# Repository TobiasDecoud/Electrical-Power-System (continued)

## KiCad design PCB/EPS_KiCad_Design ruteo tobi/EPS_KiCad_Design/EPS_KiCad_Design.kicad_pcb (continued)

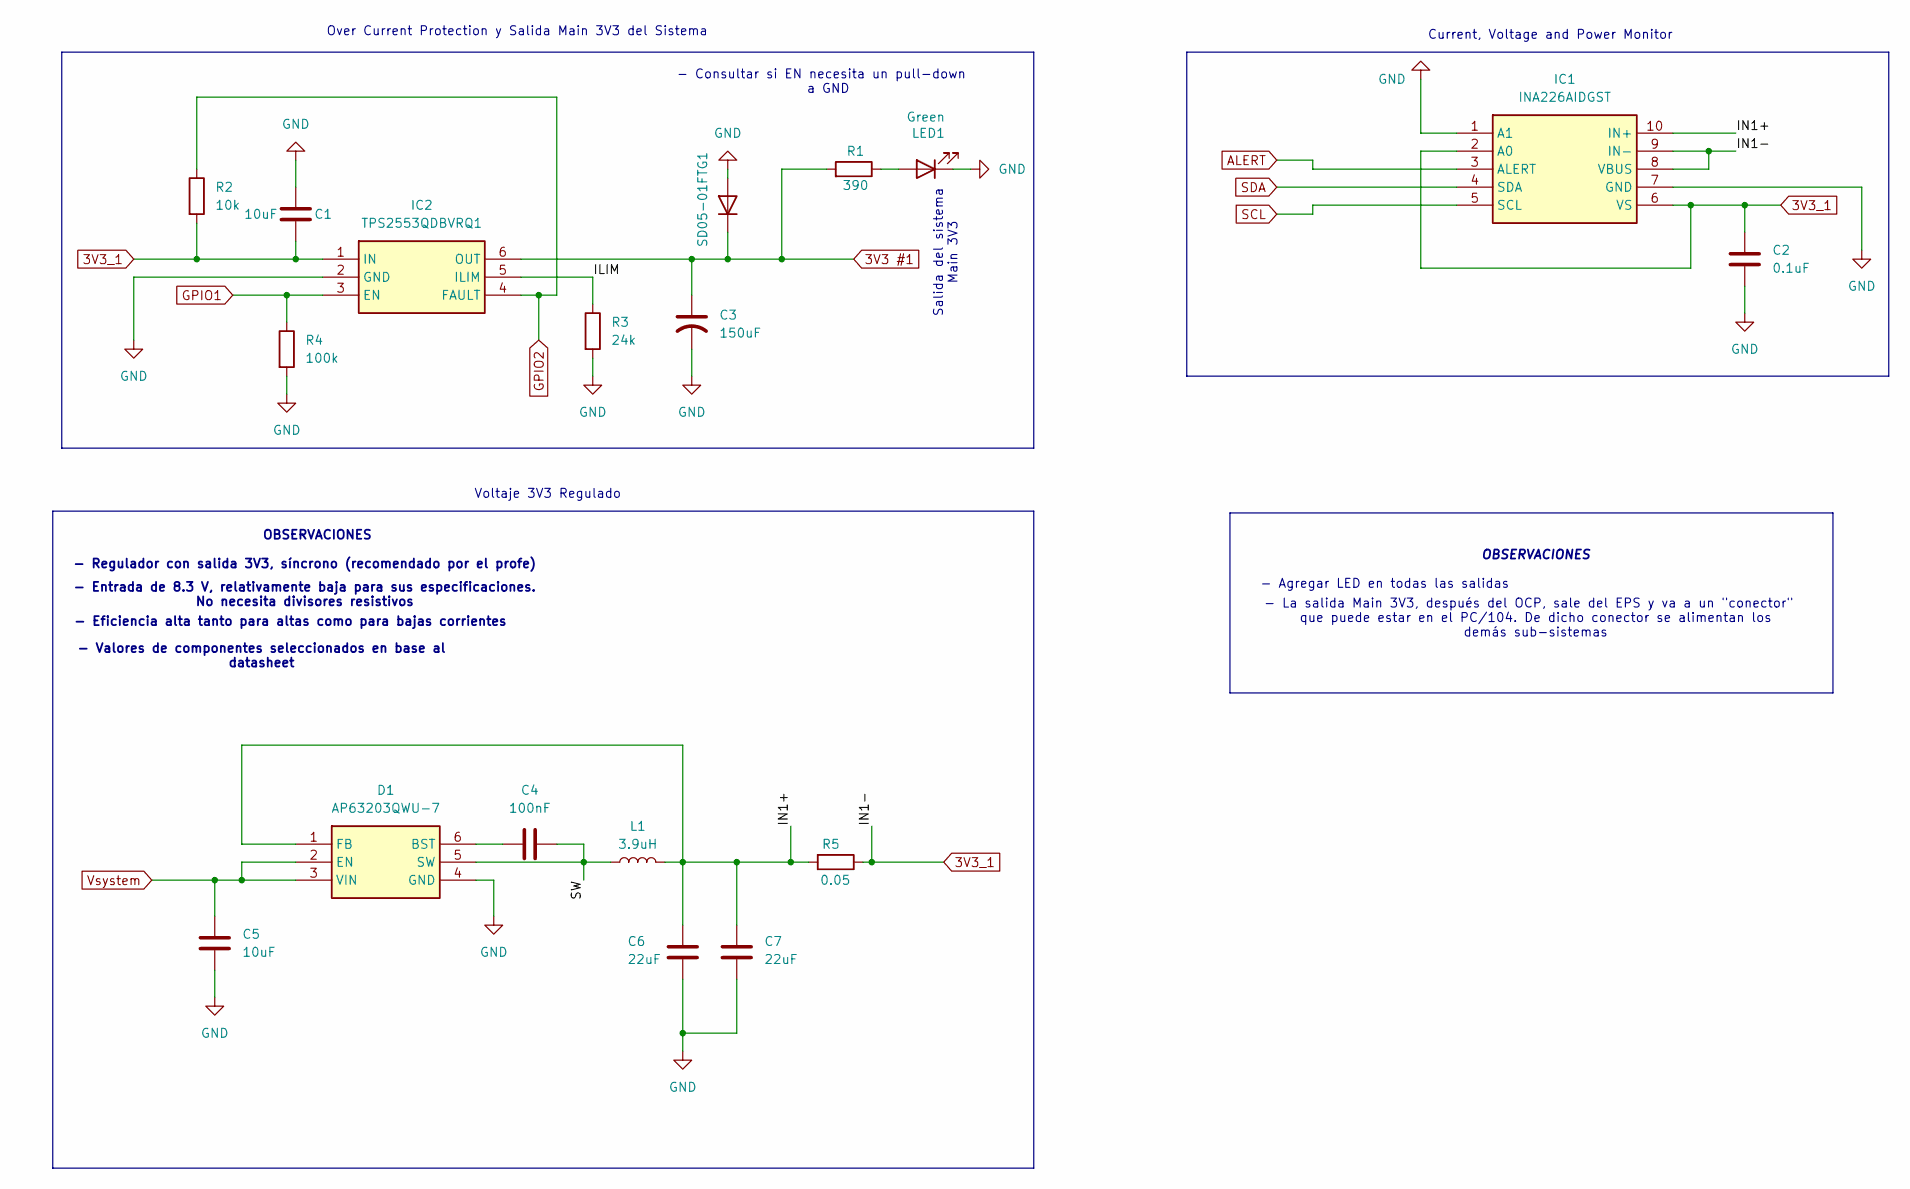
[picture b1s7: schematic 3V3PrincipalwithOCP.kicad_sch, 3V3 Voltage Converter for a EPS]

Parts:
C1, C5: 10uF; C_0805_2012Metric_Pad1.18x1.45mm_HandSolder
C2: 0.1uF; C_0805_2012Metric_Pad1.18x1.45mm_HandSolder
C3: 150uF; CAPPM3528X210N
C4: 100nF; C_0805_2012Metric_Pad1.18x1.45mm_HandSolder
C6, C7: 22uF; C_0805_2012Metric_Pad1.18x1.45mm_HandSolder
D1: AP63203QWU-7; SOT95P280X100-6N; Mouser Part Number 621-AP63203QWU-7
IC1: INA226AIDGST; SOP50P490X110-10N; Mouser Part Number 595-INA226AIDGST
IC2: TPS2553QDBVRQ1; SOT95P280X145-6N; Mouser Part Number 595-TPS2553QDBVRQ1
L1: 3.9uH; ASPI0628150MT1
LED1: Green; LED_0805_2012Metric_Pad1.15x1.40mm_HandSolder
R1: 390; R_0805_2012Metric_Pad1.20x1.40mm_HandSolder
R2: 10k; R_0805_2012Metric_Pad1.20x1.40mm_HandSolder
R3: 24k; R_0805_2012Metric_Pad1.20x1.40mm_HandSolder
R4: 100k; R_0805_2012Metric_Pad1.20x1.40mm_HandSolder
R5: 0.05; R_0805_2012Metric_Pad1.20x1.40mm_HandSolder
SD05-01FTG1: D; SOD2613X114N

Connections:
3V3 #1: C3.1, IC2.6 (OUT), R1.2, SD05-01FTG1.1 (K); also elsewhere on the board
3V3_1: C1.1, C2.1, IC1.2 (A0), IC1.6 (VS), IC1.8 (VBUS), IC1.9 (IN-), IC2.1 (IN), R2.2, R5.1; also elsewhere on the board
/Voltage Converter/3V3 Principal + OCP/ILIM: IC2.5 (ILIM), R3.1
/Voltage Converter/3V3 Principal + OCP/IN1+: C6.1, C7.1, D1.1 (FB), IC1.10 (IN+), L1.2, R5.2
/Voltage Converter/3V3 Principal + OCP/SW: C4.2, D1.5 (SW), L1.1
ALERT: IC1.3 (ALERT); also elsewhere on the board
GND: C1.2, C2.2, C3.2, C5.2, C6.2, C7.2, D1.4 (GND), IC1.1 (A1), IC1.7 (GND), IC2.2 (GND), LED1.1 (K), R3.2, R4.2, SD05-01FTG1.2 (A); also elsewhere on the board
GPIO1: IC2.3 (EN), R4.1; also elsewhere on the board
GPIO2: IC2.4 (FAULT), R2.1; also elsewhere on the board
unnamed: C4.1, D1.6 (BST)
unnamed: LED1.2 (A), R1.1
SCL: IC1.5 (SCL); also elsewhere on the board
SDA: IC1.4 (SDA); also elsewhere on the board
Vsystem: C5.1, D1.2 (EN), D1.3 (VIN); also elsewhere on the board

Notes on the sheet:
- Consultar si EN necesita un pull-down a GND
Voltaje 3V3 Regulado
Current, Voltage and Power Monitor
- Entrada de 8.3 V, relativamente baja para sus especificaciones. No necesita divisores resistivos
- Regulador con salida 3V3, síncrono (recomendado por el profe)
- Eficiencia alta tanto para altas como para bajas corrientes
OBSERVACIONES
- Valores de componentes seleccionados en base al datasheet
Salida del sistema Main 3V3
Over Current Protection y Salida Main 3V3 del Sistema
- Agregar LED en todas las salidas
- La salida Main 3V3, después del OCP, sale del EPS y va a un "conector" que puede estar en el PC/104. De dicho conector se alimentan los demás sub-sistemas

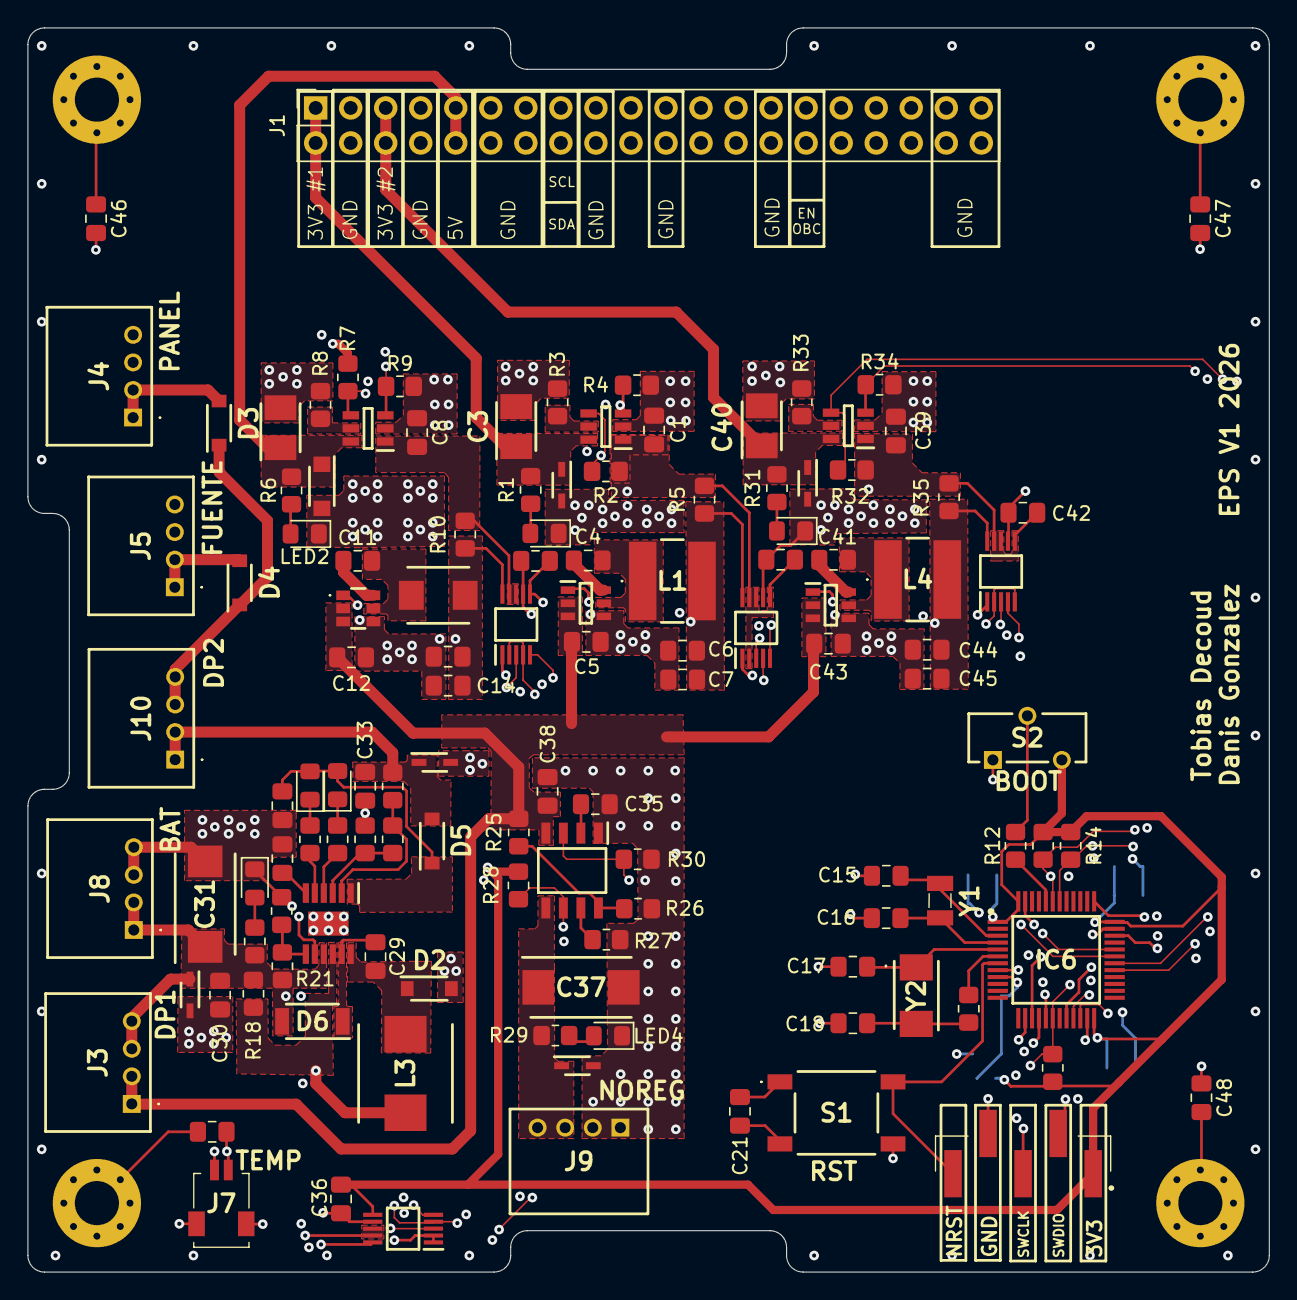
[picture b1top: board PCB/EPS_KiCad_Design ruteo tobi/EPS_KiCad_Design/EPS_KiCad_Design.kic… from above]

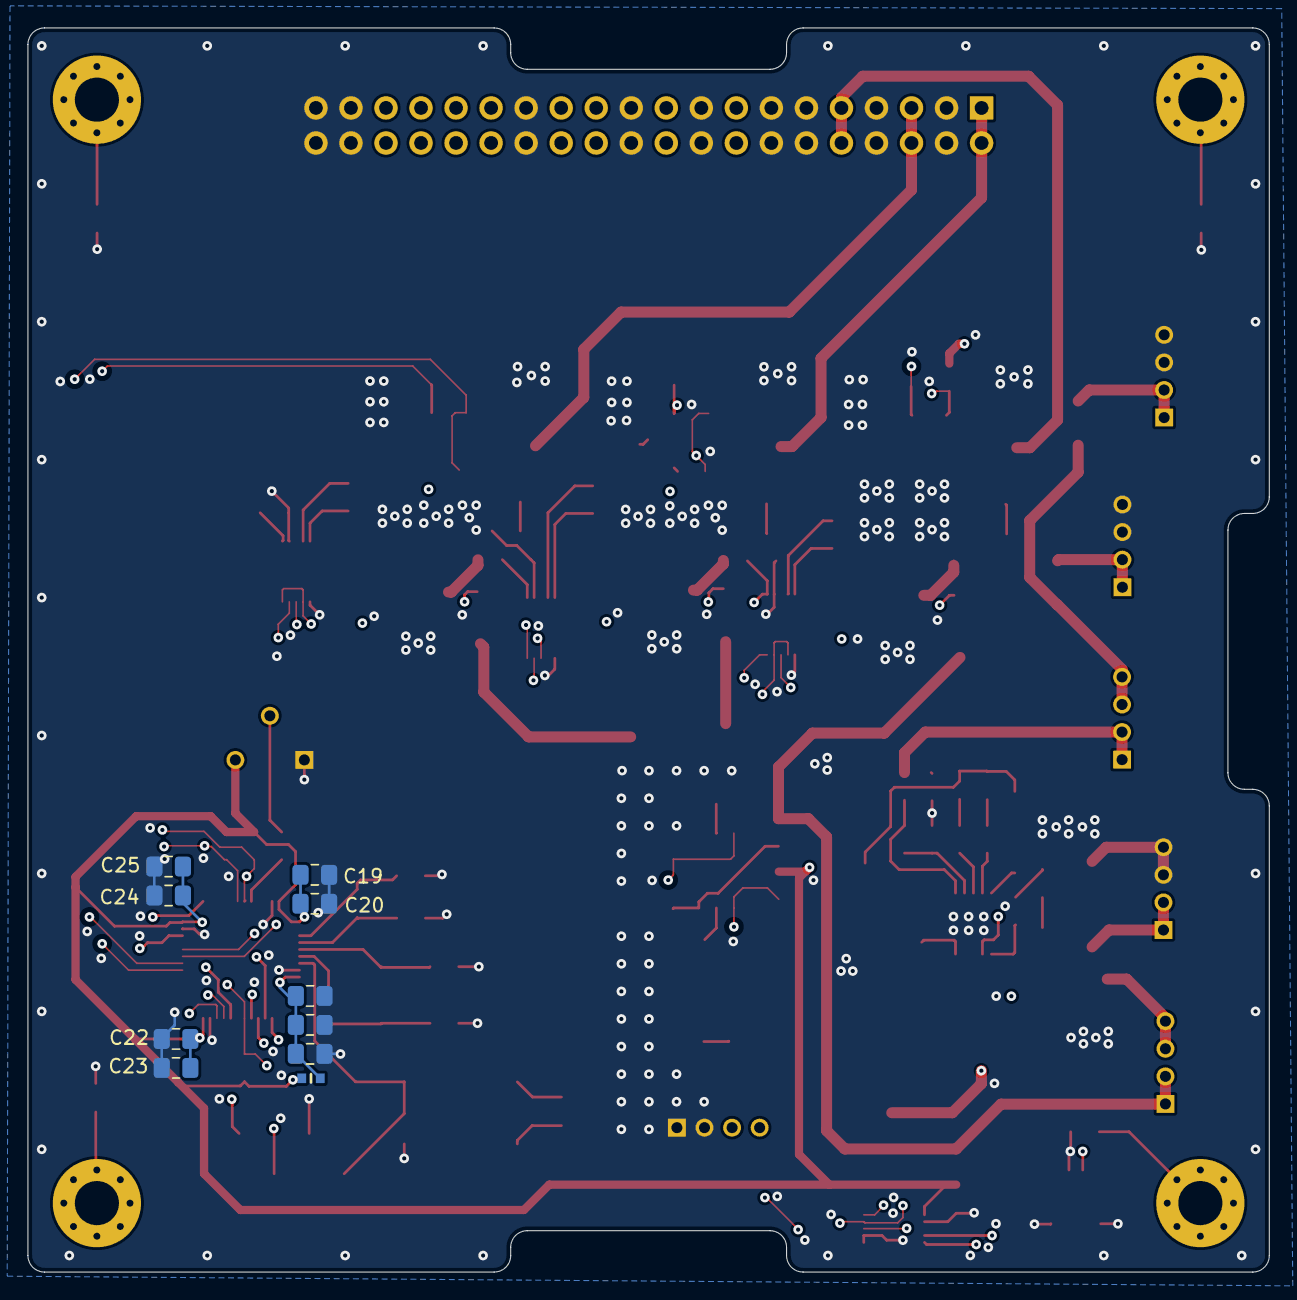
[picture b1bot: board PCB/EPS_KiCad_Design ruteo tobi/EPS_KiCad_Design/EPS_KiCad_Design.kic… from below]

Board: 4 copper layers, 90.0 x 90.2 mm, 137 parts (10 on the bottom side), 78 nets.

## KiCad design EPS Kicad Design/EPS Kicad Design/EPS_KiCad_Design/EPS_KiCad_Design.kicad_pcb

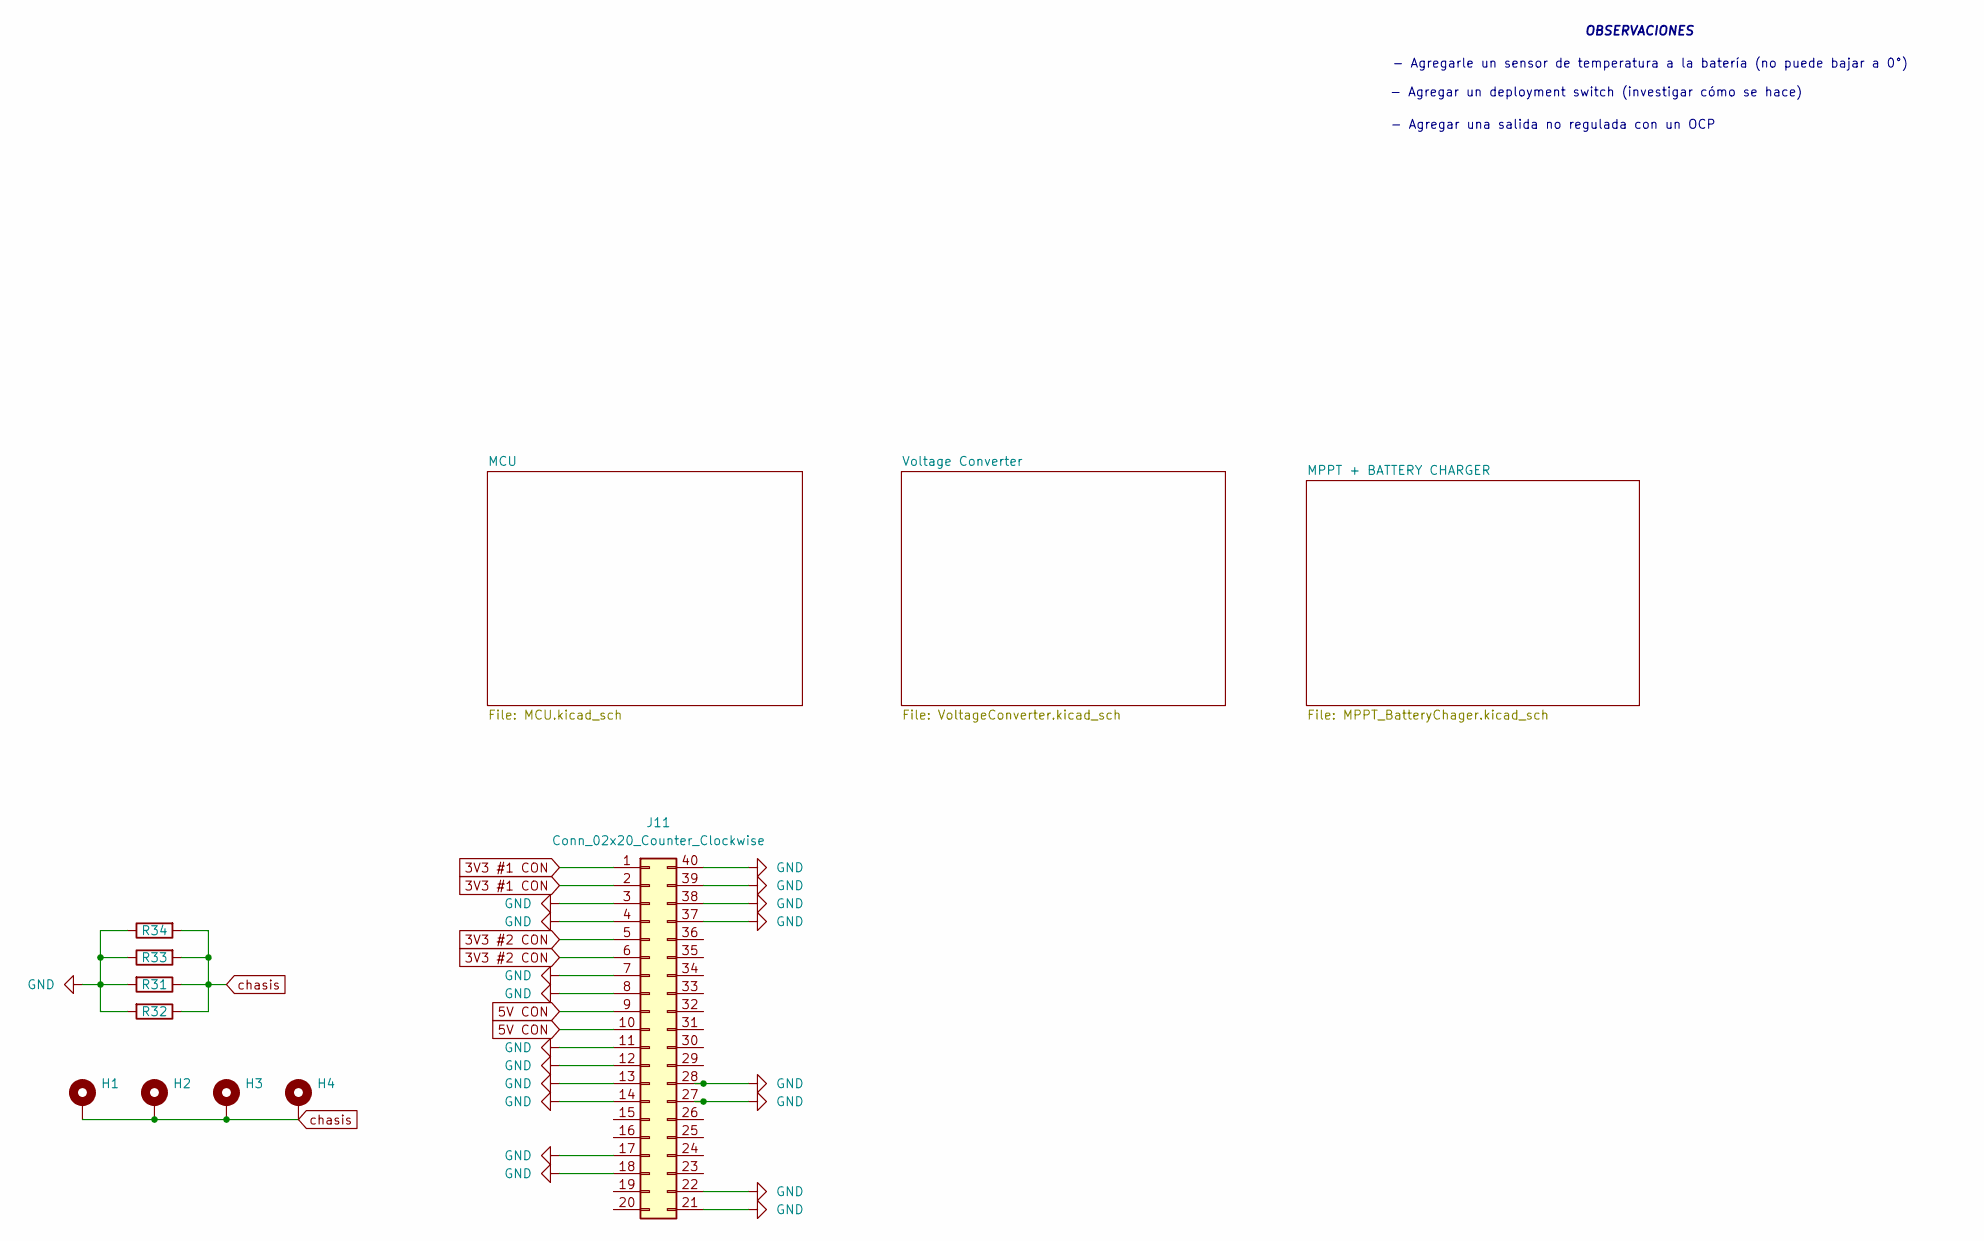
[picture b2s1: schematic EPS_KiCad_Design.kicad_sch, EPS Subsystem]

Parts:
H1, H2, H3, H4: MountingHole_Pad
J11: Conn_02x20_Counter_Clockwise; PinSocket_2x20_P2.54mm_Vertical
R31, R32, R33, R34: R_0805_2012Metric_Pad1.20x1.40mm_HandSolder

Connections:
3V3 #1 CON: J11.1, J11.2; also elsewhere on the board
3V3 #2 CON: J11.5, J11.6; also elsewhere on the board
5V CON: J11.9, J11.10; also elsewhere on the board
GND: J11.3, J11.4, J11.7, J11.8, J11.11, J11.12, J11.13, J11.14, J11.17, J11.18, J11.21, J11.22, J11.27, J11.28, J11.37, J11.38, J11.39, J11.40, R31.2, R32.2, R33.1, R34.1; also elsewhere on the board
chasis: H1.1, H2.1, H3.1, H4.1, R31.1, R32.1, R33.2, R34.2

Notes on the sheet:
OBSERVACIONES
- Agregar un deployment switch (investigar cómo se hace)
- Agregarle un sensor de temperatura a la batería (no puede bajar a 0°)
- Agregar una salida no regulada con un OCP

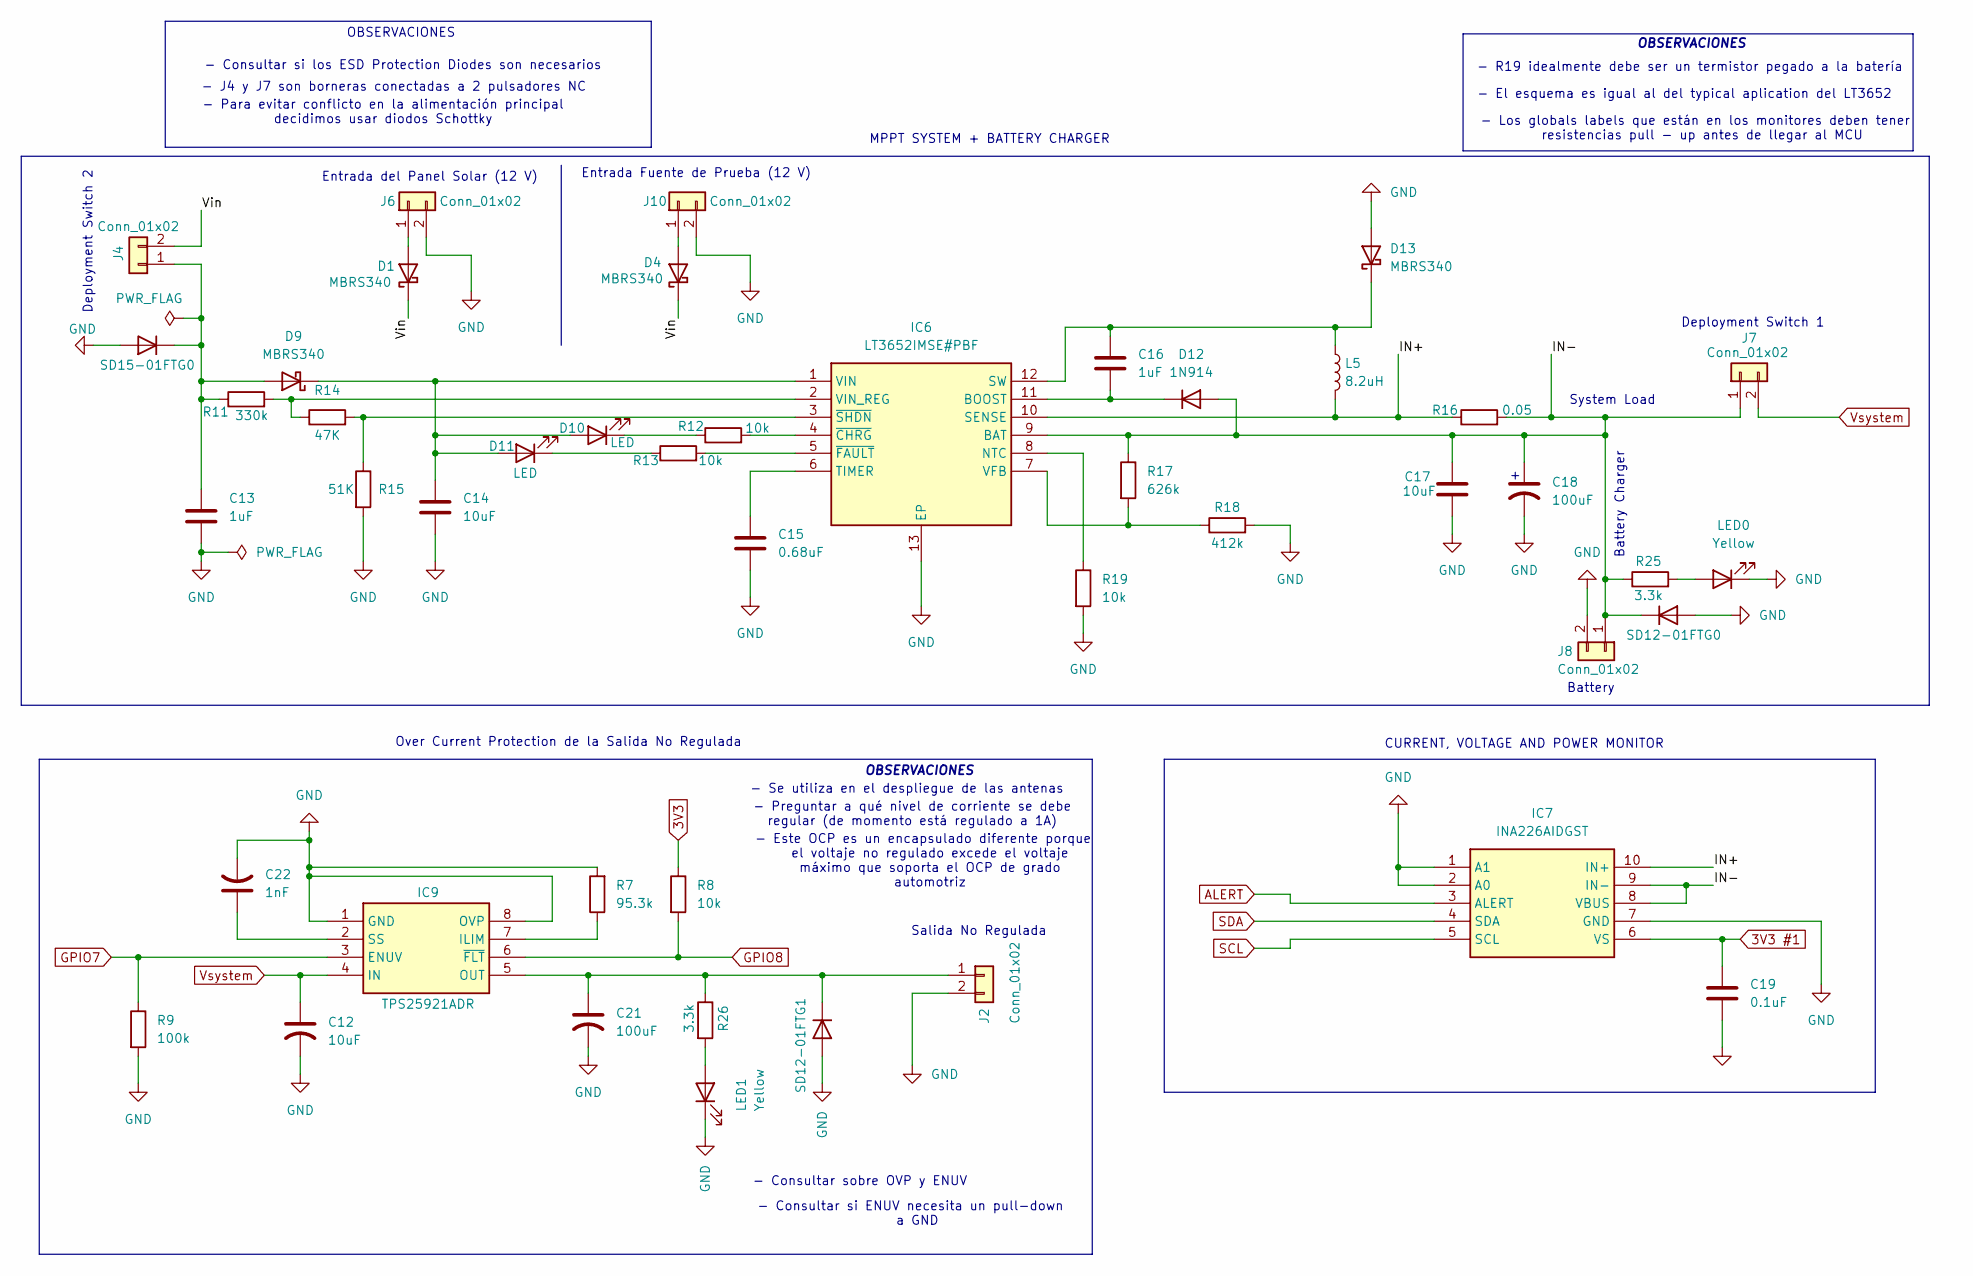
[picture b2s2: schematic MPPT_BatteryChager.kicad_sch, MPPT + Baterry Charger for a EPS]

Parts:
C12: 10uF; CP_EIA-7343-30_AVX-N_HandSolder
C13, C16: 1uF; C_0805_2012Metric_Pad1.18x1.45mm_HandSolder
C14, C17: 10uF; C_0805_2012Metric_Pad1.18x1.45mm_HandSolder
C15: 0.68uF; C_0805_2012Metric_Pad1.18x1.45mm_HandSolder
C18, C21: 100uF; CP_EIA-7343-30_AVX-N_HandSolder
C19: 0.1uF; C_0805_2012Metric_Pad1.18x1.45mm_HandSolder
C22: 1nF; CP_EIA-7343-30_AVX-N_HandSolder
D1, D4, D9, D13: MBRS340; D_SMC
D10, D11: LED; LED_0805_2012Metric_Pad1.15x1.40mm_HandSolder
D12: 1N914; 1N4148WQ13F
IC6: LT3652IMSE#PBF; SOP65P490X110-13N; Mouser Part Number 584-LT3652IMSE#PBF
IC7: INA226AIDGST; SOP50P490X110-10N; Mouser Part Number 595-INA226AIDGST
IC9: TPS25921ADR; SOIC127P600X175-8N; Mouser Part Number 595-TPS25921ADR
J2, J4, J6, J7, J8, J10: Conn_01x02
L5: 8.2uH; INDPM6965X300N
LED0, LED1: Yellow; LED_0805_2012Metric_Pad1.15x1.40mm_HandSolder
R7: 95.3k; R_0805_2012Metric_Pad1.20x1.40mm_HandSolder
R8, R12, R13, R19: 10k; R_0805_2012Metric_Pad1.20x1.40mm_HandSolder
R9: 100k; R_0805_2012Metric_Pad1.20x1.40mm_HandSolder
R11: 330k; R_0805_2012Metric_Pad1.20x1.40mm_HandSolder
R14: 47K; R_0805_2012Metric_Pad1.20x1.40mm_HandSolder
R15: 51K; R_0805_2012Metric_Pad1.20x1.40mm_HandSolder
R16: 0.05; R_2512_6332Metric_Pad1.40x3.35mm_HandSolder
R17: 626k; R_0805_2012Metric_Pad1.20x1.40mm_HandSolder
R18: 412k; R_0805_2012Metric_Pad1.20x1.40mm_HandSolder
R25, R26: 3.3k; R_0805_2012Metric_Pad1.20x1.40mm_HandSolder
SD12-01FTG0, SD12-01FTG1: SOD2613X114N
SD15-01FTG0: D; SOD2613X114N

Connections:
3V3: R8.1; also elsewhere on the board
3V3 #1: C19.1, IC7.6 (VS); also elsewhere on the board
/MPPT + BATTERY CHARGER/IN+: IC6.10 (SENSE), IC7.10 (IN+), L5.2, R16.1
/MPPT + BATTERY CHARGER/IN-: C17.1, C18.1, D12.2 (A), IC6.9 (BAT), IC7.8 (VBUS), IC7.9 (IN-), J7.1, J8.1, R16.2, R17.1, R25.1, SD12-01FTG0.1 (K)
/MPPT + BATTERY CHARGER/Vin: D1.1 (K), D4.1 (K), J4.2
ALERT: IC7.3 (ALERT); also elsewhere on the board
GND: C12.2, C13.2, C14.2, C15.2, C17.2, C18.2, C19.2, C21.2, C22.2, D13.2 (A), IC6.13 (EP), IC7.1 (A1), IC7.2 (A0), IC7.7 (GND), IC9.1 (GND), IC9.8 (OVP), J2.2, J6.2, J8.2, J10.2, LED0.1 (K), LED1.1 (K), R7.2, R9.2, R15.2, R18.2, R19.2, SD12-01FTG0.2 (A), SD12-01FTG1.2 (A), SD15-01FTG0.2 (A); also elsewhere on the board
GPIO7: IC9.3 (ENUV), R9.1; also elsewhere on the board
GPIO8: IC9.6 (~FLT), R8.2; also elsewhere on the board
unnamed: D1.2 (A), J6.1
unnamed: D4.2 (A), J10.1
unnamed: C13.1, D9.2 (A), J4.1, R11.1, SD15-01FTG0.1 (K)
unnamed: C14.1, D9.1 (K), D10.2 (A), D11.2 (A), IC6.1 (VIN)
unnamed: D10.1 (K), R12.1
unnamed: D11.1 (K), R13.1
unnamed: C16.2, D12.1 (K), IC6.11 (BOOST)
unnamed: C16.1, D13.1 (K), IC6.12 (SW), L5.1
unnamed: IC6.8 (NTC), R19.1
unnamed: C15.1, IC6.6 (TIMER)
unnamed: IC6.7 (VFB), R17.2, R18.1
unnamed: IC6.2 (VIN_REG), R11.2, R14.1
unnamed: IC6.4 (~CHRG), R12.2
unnamed: IC6.5 (~FAULT), R13.2
unnamed: IC6.3 (~SHDN), R14.2, R15.1
unnamed: IC9.7 (ILIM), R7.1
unnamed: C21.1, IC9.5 (OUT), J2.1, R26.1, SD12-01FTG1.1 (K)
unnamed: C22.1, IC9.2 (SS)
unnamed: LED0.2 (A), R25.2
unnamed: LED1.2 (A), R26.2
SCL: IC7.5 (SCL); also elsewhere on the board
SDA: IC7.4 (SDA); also elsewhere on the board
Vsystem: C12.1, IC9.4 (IN), J7.2; also elsewhere on the board

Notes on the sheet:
CURRENT, VOLTAGE AND POWER MONITOR
- Se utiliza en el despliegue de las antenas
System Load
OBSERVACIONES
Entrada del Panel Solar (12 V)
- Los globals labels que están en los monitores deben tener resistencias pull - up antes de llegar al MCU
- Para evitar conflicto en la alimentación principal decidimos usar diodos Schottky
Battery Charger
- Este OCP es un encapsulado diferente porque el voltaje no regulado excede el voltaje máximo que soporta el OCP de grado automotriz
- El esquema es igual al del typical aplication del LT3652
Over Current Protection de la Salida No Regulada
- Consultar si ENUV necesita un pull-down a GND
Deployment Switch 1
Entrada Fuente de Prueba (12 V)
Deployment Switch 2
- R19 idealmente debe ser un termistor pegado a la batería
- J4 y J7 son borneras conectadas a 2 pulsadores NC
- Consultar si los ESD Protection Diodes son necesarios
- Consultar sobre OVP y ENUV
Salida No Regulada
- Preguntar a qué nivel de corriente se debe regular (de momento está regulado a 1A)
Battery
MPPT SYSTEM + BATTERY CHARGER

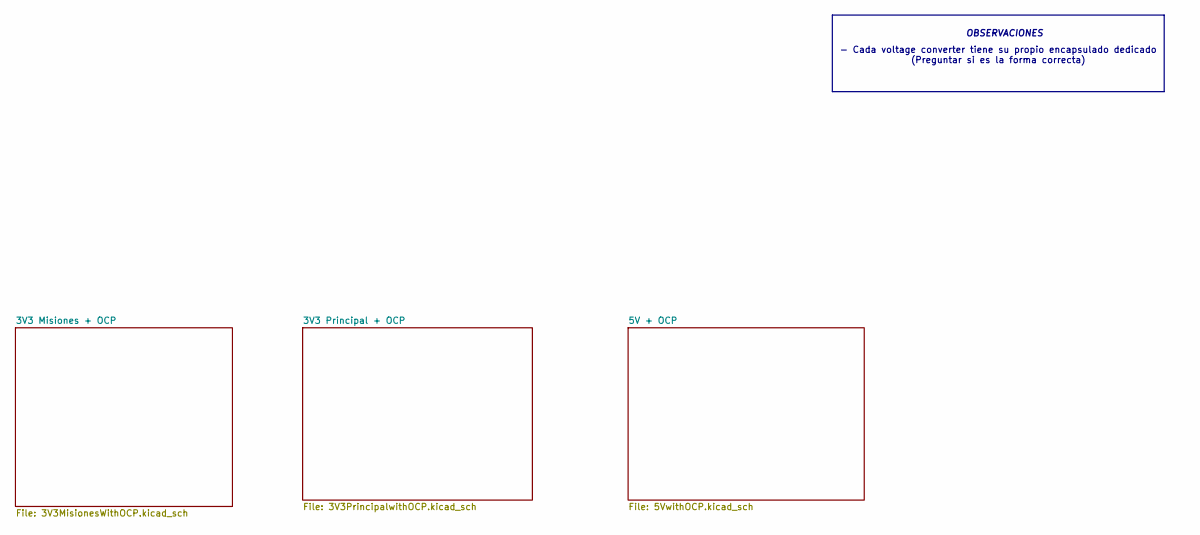
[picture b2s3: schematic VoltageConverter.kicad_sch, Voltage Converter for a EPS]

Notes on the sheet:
- Cada voltage converter tiene su propio encapsulado dedicado (Preguntar si es la forma correcta)
OBSERVACIONES

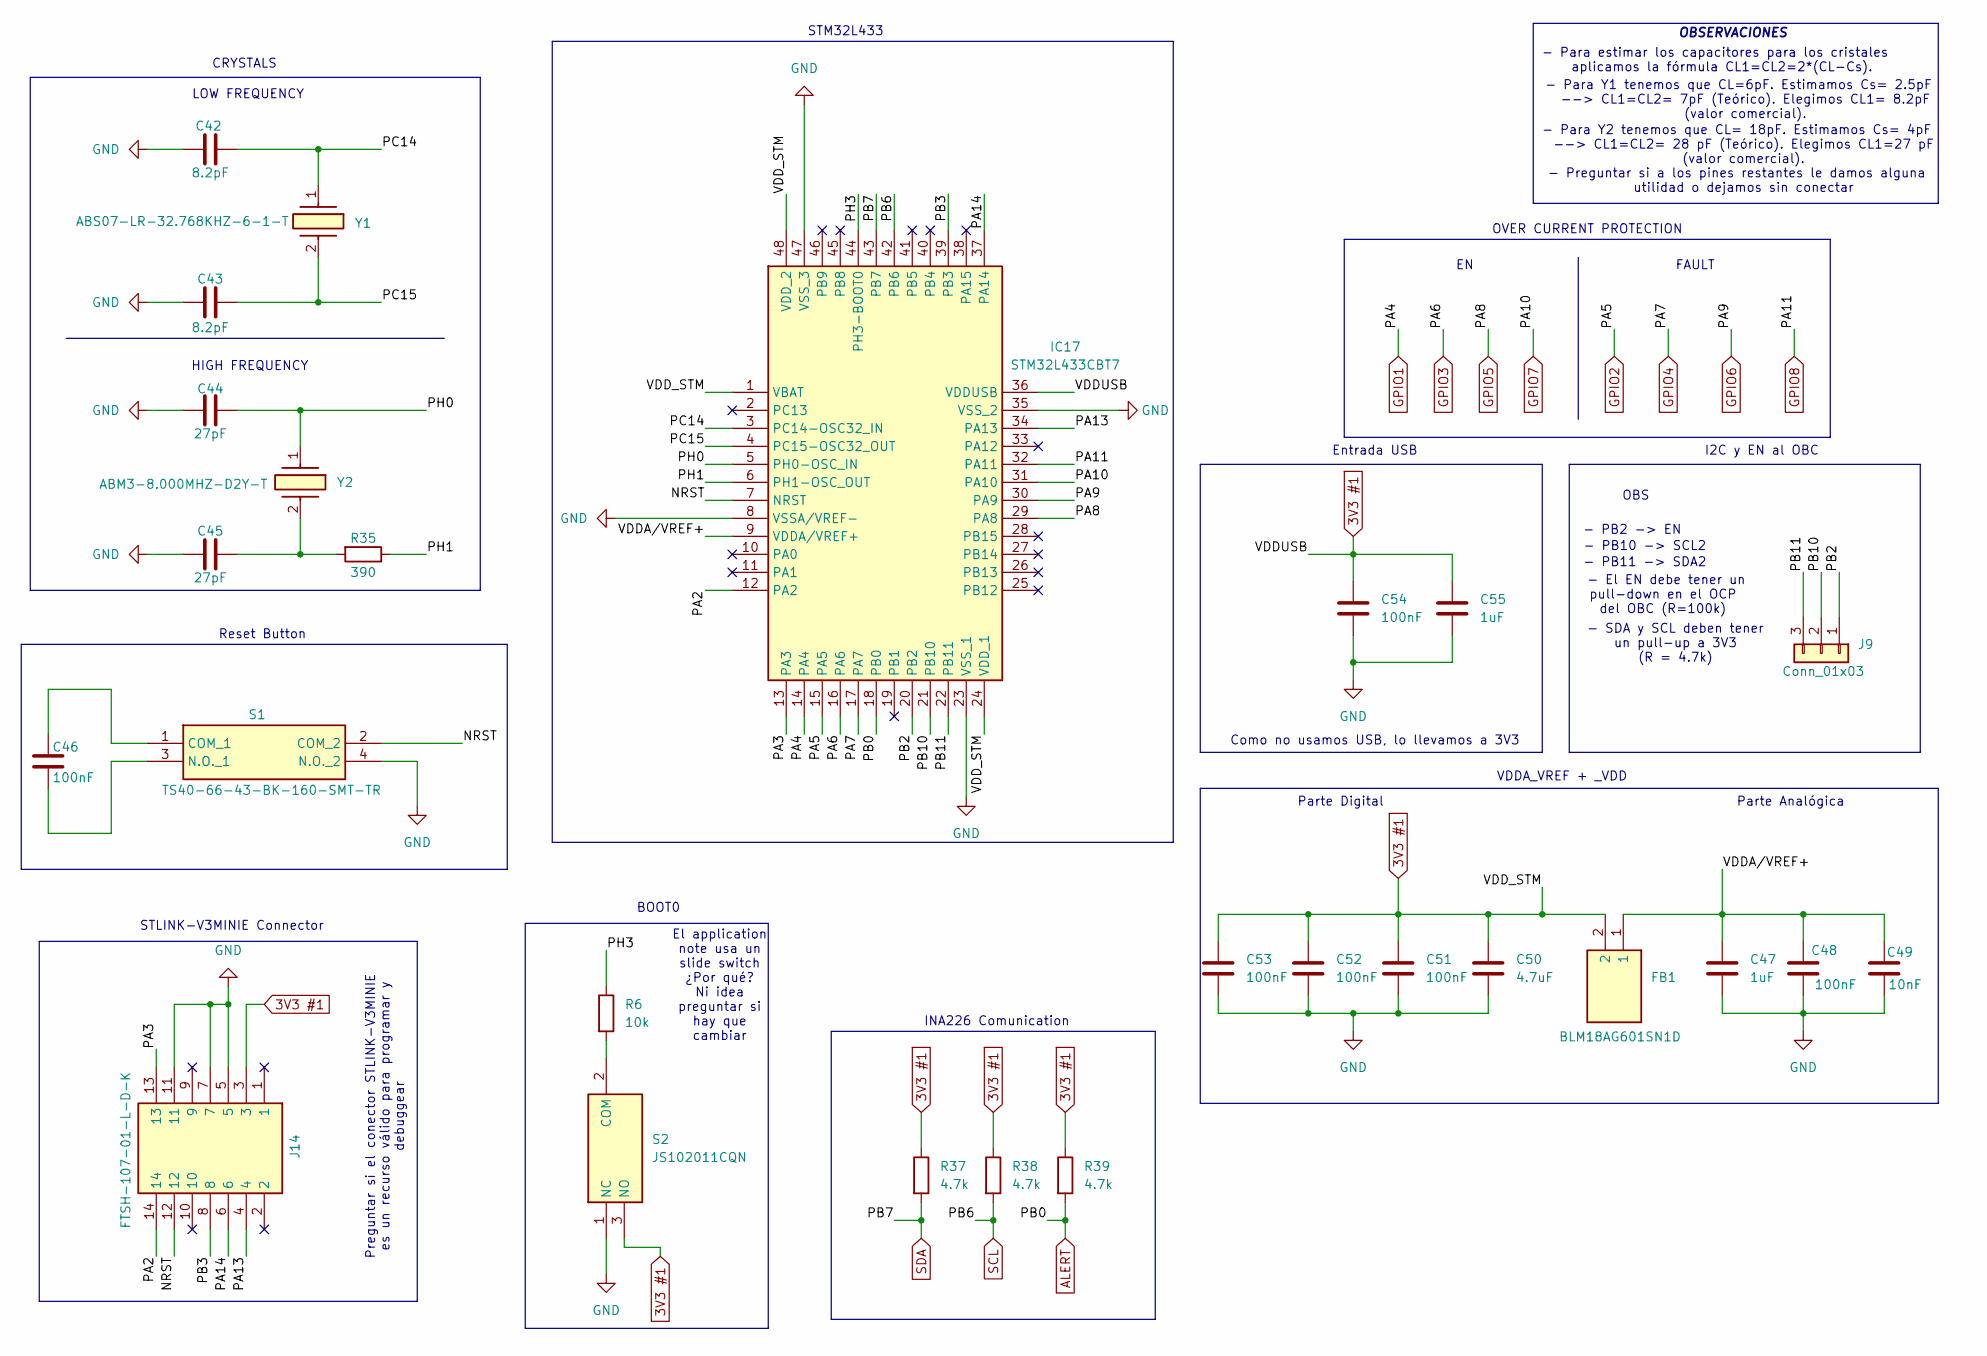
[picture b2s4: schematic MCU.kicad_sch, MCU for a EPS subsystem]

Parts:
C42: 8.2pF; C_0805_2012Metric_Pad1.18x1.45mm_HandSolder
C43: 8.2pF
C44: 27pF; C_0805_2012Metric_Pad1.18x1.45mm_HandSolder
C45: 27pF
C46, C48, C51, C52, C53, C54: 100nF; C_0805_2012Metric_Pad1.18x1.45mm_HandSolder
C47, C55: 1uF; C_0805_2012Metric_Pad1.18x1.45mm_HandSolder
C49: 10nF; C_0805_2012Metric_Pad1.18x1.45mm_HandSolder
C50: 4.7uF; C_0805_2012Metric_Pad1.18x1.45mm_HandSolder
FB1: BLM18AG601SN1D; BLM18SP221SN1B; Mouser Part Number 81-BLM11A601S
IC17: STM32L433CBT7; QFP50P900X900X160-48N; Mouser Part Number 511-STM32L433CBT7
J9: Conn_01x03
J14: FTSH-107-01-L-D-K; FTSH-107-XX-YYY-D-K; Mouser Part Number 200-FTSH10701LDK
R6: 10k; R_0805_2012Metric_Pad1.20x1.40mm_HandSolder
R35: 390; R_0805_2012Metric_Pad1.20x1.40mm_HandSolder
R37, R38, R39: 4.7k; R_0805_2012Metric_Pad1.20x1.40mm_HandSolder
S1: TS40-66-43-BK-160-SMT-TR; TS406643BK160SMTTR; Manufacturer_Part_Number TS40-66-43-BK-160-SMT-TR
S2: JS102011CQN; Mouser Part Number 611-JS102011CQN
Y1: ABS07-LR-32.768KHZ-6-1-T; ABS07LR32768kHz61T; Mouser Part Number 815-ABS07LR32.76-61T
Y2: ABM3-8.000MHZ-D2Y-T; ABM3; Mouser Part Number 815-ABM3-8-D2Y-T

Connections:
3V3 #1: C50.1, C51.1, C52.1, C53.1, C54.1, C55.1, FB1.2, IC17.1 (VBAT), IC17.24 (VDD_1), IC17.36 (VDDUSB), IC17.48 (VDD_2), J14.3, R37.1, R38.1, R39.1, S2.3 (NO); also elsewhere on the board
/MCU/NRST: IC17.7 (NRST), J14.12, S1.2 (COM_2)
/MCU/PA2: IC17.12 (PA2), J14.14
/MCU/PA3: IC17.13 (PA3), J14.13
/MCU/PA13: IC17.34 (PA13), J14.4
/MCU/PA14: IC17.37 (PA14), J14.6
/MCU/PB2: IC17.20 (PB2), J9.1
/MCU/PB3: IC17.39 (PB3), J14.8
/MCU/PB10: IC17.21 (PB10), J9.2
/MCU/PB11: IC17.22 (PB11), J9.3
/MCU/PC14: C42.2, IC17.3 (PC14-OSC32_IN), Y1.1
/MCU/PC15: C43.2, IC17.4 (PC15-OSC32_OUT), Y1.2
/MCU/PH0: C44.1, IC17.5 (PH0-OSC_IN), Y2.1
/MCU/PH1: IC17.6 (PH1-OSC_OUT), R35.1
/MCU/PH3: IC17.44 (PH3-BOOT0), R6.1
/MCU/VDDA/VREF+: C47.1, C48.1, C49.1, FB1.1, IC17.9 (VDDA/VREF+)
ALERT: IC17.18 (PB0), R39.2; also elsewhere on the board
GND: C42.1, C43.1, C44.2, C45.2, C47.2, C48.2, C49.2, C50.2, C51.2, C52.2, C53.2, C54.2, C55.2, IC17.8 (VSSA/VREF-), IC17.23 (VSS_1), IC17.35 (VSS_2), IC17.47 (VSS_3), J14.5, J14.7, J14.11, S1.4 (N.O._2), S2.1 (NC); also elsewhere on the board
GPIO1: IC17.14 (PA4); also elsewhere on the board
GPIO2: IC17.15 (PA5); also elsewhere on the board
GPIO3: IC17.16 (PA6); also elsewhere on the board
GPIO4: IC17.17 (PA7); also elsewhere on the board
GPIO5: IC17.29 (PA8); also elsewhere on the board
GPIO6: IC17.30 (PA9); also elsewhere on the board
GPIO7: IC17.31 (PA10); also elsewhere on the board
GPIO8: IC17.32 (PA11); also elsewhere on the board
unnamed: C45.1, R35.2, Y2.2
unnamed: C46.1, S1.1 (COM_1)
unnamed: C46.2, S1.3 (N.O._1)
unnamed: R6.2, S2.2 (COM)
SCL: IC17.42 (PB6), R38.2; also elsewhere on the board
SDA: IC17.43 (PB7), R37.2; also elsewhere on the board

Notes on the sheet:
BOOT0
- SDA y SCL deben tener un pull-up a 3V3 (R = 4.7k)
OBSERVACIONES
LOW FREQUENCY
- PB2 -> EN
- PB10 -> SCL2
OVER CURRENT PROTECTION
- El EN debe tener un pull-down en el OCP del OBC (R=100k)
Entrada USB
- Para Y2 tenemos que CL= 18pF. Estimamos Cs= 4pF --> CL1=CL2= 28 pF (Teórico). Elegimos CL1=27 pF (valor comercial).
- PB11 -> SDA2
INA226 Comunication
- Preguntar si a los pines restantes le damos alguna utilidad o dejamos sin conectar
Parte Digital
Preguntar si el conector STLINK-V3MINIE es un recurso válido para programar y debuggear
STLINK-V3MINIE Connector
OBS
Reset Button
I2C y EN al OBC
Parte Analógica
FAULT
Como no usamos USB, lo llevamos a 3V3
VDDA_VREF + _VDD
- Para Y1 tenemos que CL=6pF. Estimamos Cs= 2.5pF --> CL1=CL2= 7pF (Teórico). Elegimos CL1= 8.2pF (valor comercial).
El application note usa un slide switch ¿Por qué? Ni idea preguntar si hay que cambiar
CRYSTALS
HIGH FREQUENCY
STM32L433
- Para estimar los capacitores para los cristales aplicamos la fórmula CL1=CL2=2*(CL-Cs).
